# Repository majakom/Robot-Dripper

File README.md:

# Robot-Dripper

Project made for Computer System Architecture at Poznań University of Technology.

## General description of the project

The goal of this project was to create a robot that is a coffee machine.
Project was finally presented at Poznań Univeristy of Technology at the event RoboDay.

This repository includes code for both [arduino UNO prototype](motor_control) and [atmega 8 final version](ask) of the robot.<br />
[This directory](motiondetector) leads to code used for testing the motion detector.<br />
[Here](Eagle) You can find an Eagle board and schemtic for the PCB.

## Links to documentation

Entire documentation of the proccess available under the following link:<br />
https://docs.google.com/document/d/1cahnLlo-Lx6Y2TZ_qJPBwkHGlFsrj01b/edit?usp=sharing&ouid=103557156073634909180&rtpof=true&sd=true

Short film on YouTube which depicts the process of creating the coffee machine:<br />
https://www.youtube.com/watch?v=yFp_BpbxnpI

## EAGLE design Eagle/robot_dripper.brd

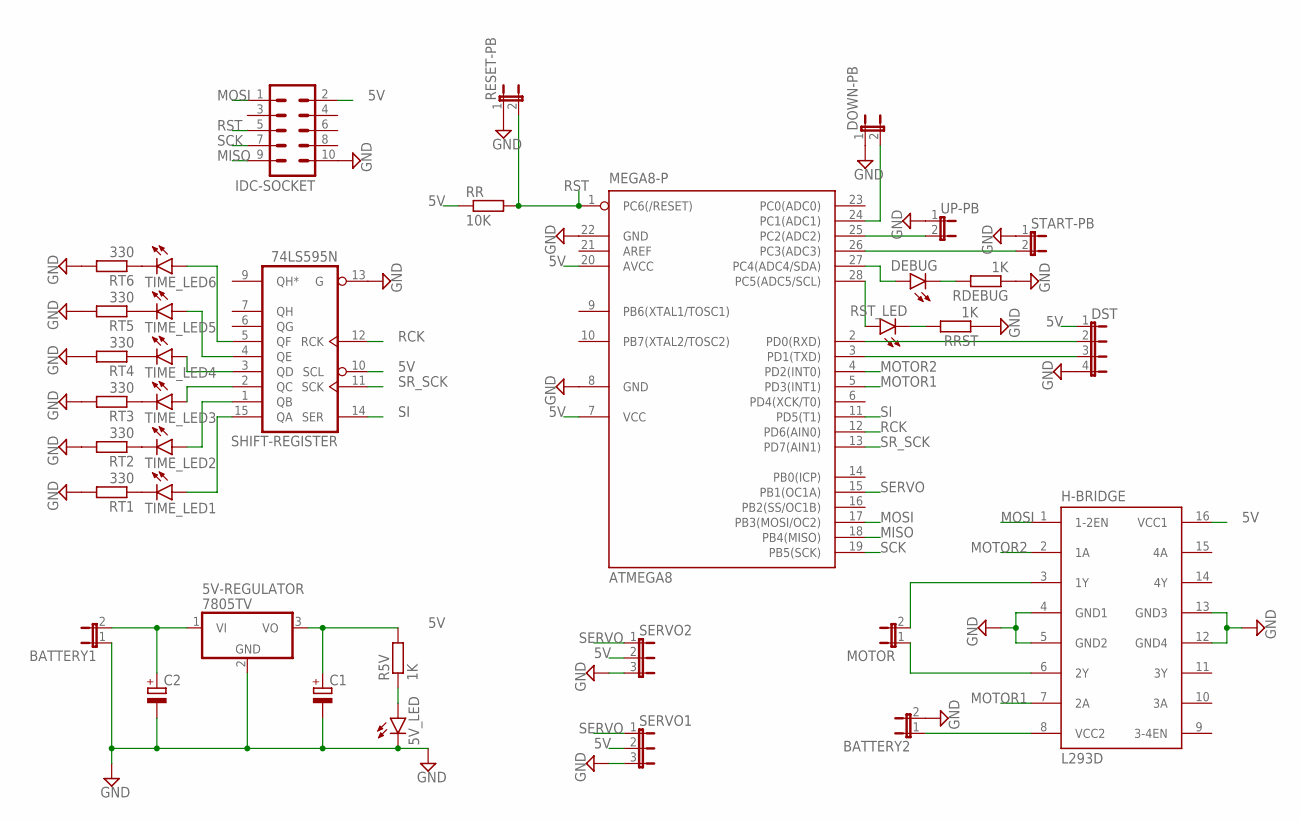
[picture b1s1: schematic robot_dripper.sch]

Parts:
5V-REGULATOR: 7805TV; TO220V
5V_LED: LED5MM
ATMEGA8: MEGA8-P; DIL28-3
BATTERY1, BATTERY2: JP1E; JP1
C1, C2: CPOL-EUE5-10.5; E5-10,5
DEBUG: LED5MM
DOWN-PB: JP1E; JP1
DST: JP4E; JP4
H-BRIDGE: L293D; DIL16
IDC-SOCKET: ML10
MOTOR: JP1E; JP1
R5V: 1K; 0207/10
RDEBUG: 1K; 0207/10
RESET-PB: JP1E; JP1
RR: 10K; 0207/10
RRST: 1K; 0207/10
RST_LED: LED5MM
RT1, RT2, RT3, RT4, RT5, RT6: 330; 0207/10
SERVO1, SERVO2: JP2E; JP2
SHIFT-REGISTER: 74LS595N; DIL16
START-PB: JP1E; JP1
TIME_LED1, TIME_LED2, TIME_LED3, TIME_LED4, TIME_LED5, TIME_LED6: LED5MM
UP-PB: JP1E; JP1

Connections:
5V: 5V-REGULATOR.3 (VO), ATMEGA8.7 (VCC), ATMEGA8.20 (AVCC), C1.+, DST.1, H-BRIDGE.16 (VCC1), IDC-SOCKET.2, R5V.2, RR.1, SERVO1.2, SERVO2.2, SHIFT-REGISTER.10 (SCL), SHIFT-REGISTER.16 (VCC)
GND: 5V-REGULATOR.2 (GND), 5V_LED.K (C), ATMEGA8.8 (GND), ATMEGA8.22 (GND), BATTERY1.1, BATTERY2.2, C1.-, C2.-, DOWN-PB.1, DST.4, H-BRIDGE.4 (GND1), H-BRIDGE.5 (GND2), H-BRIDGE.12 (GND4), H-BRIDGE.13 (GND3), IDC-SOCKET.10, RDEBUG.1, RESET-PB.1, RRST.1, RT1.2, RT2.2, RT3.2, RT4.2, RT5.2, RT6.2, SERVO1.3, SERVO2.3, SHIFT-REGISTER.8 (GND), SHIFT-REGISTER.13 (G), START-PB.1, UP-PB.1
MISO: ATMEGA8.18 (PB4(MISO)), IDC-SOCKET.9
MOSI: ATMEGA8.17 (PB3(MOSI/OC2)), H-BRIDGE.1 (1-2EN), IDC-SOCKET.1
MOTOR1: ATMEGA8.5 (PD3(INT1)), H-BRIDGE.7 (2A)
MOTOR2: ATMEGA8.4 (PD2(INT0)), H-BRIDGE.2 (1A)
unnamed: ATMEGA8.28 (PC5(ADC5/SCL)), RST_LED.A
unnamed: 5V_LED.A, R5V.1
unnamed: RRST.2, RST_LED.K (C)
unnamed: ATMEGA8.27 (PC4(ADC4/SDA)), DEBUG.A
unnamed: DEBUG.K (C), RDEBUG.2
unnamed: ATMEGA8.26 (PC3(ADC3)), START-PB.2
unnamed: ATMEGA8.25 (PC2(ADC2)), UP-PB.2
unnamed: ATMEGA8.24 (PC1(ADC1)), DOWN-PB.2
unnamed: ATMEGA8.2 (PD0(RXD)), DST.2
unnamed: ATMEGA8.3 (PD1(TXD)), DST.3
unnamed: H-BRIDGE.6 (2Y), MOTOR.1
unnamed: SHIFT-REGISTER.15 (QA), TIME_LED1.A
unnamed: SHIFT-REGISTER.1 (QB), TIME_LED2.A
unnamed: SHIFT-REGISTER.2 (QC), TIME_LED3.A
unnamed: H-BRIDGE.3 (1Y), MOTOR.2
unnamed: SHIFT-REGISTER.3 (QD), TIME_LED4.A
unnamed: SHIFT-REGISTER.4 (QE), TIME_LED5.A
unnamed: SHIFT-REGISTER.5 (QF), TIME_LED6.A
unnamed: RT1.1, TIME_LED1.K (C)
unnamed: RT2.1, TIME_LED2.K (C)
unnamed: RT3.1, TIME_LED3.K (C)
unnamed: RT4.1, TIME_LED4.K (C)
unnamed: RT5.1, TIME_LED5.K (C)
unnamed: RT6.1, TIME_LED6.K (C)
unnamed: BATTERY2.1, H-BRIDGE.8 (VCC2)
unnamed: 5V-REGULATOR.1 (VI), BATTERY1.2, C2.+
RCK: ATMEGA8.12 (PD6(AIN0)), SHIFT-REGISTER.12 (RCK)
RST: ATMEGA8.1 (PC6(/RESET)), IDC-SOCKET.5, RESET-PB.2, RR.2
SCK: ATMEGA8.19 (PB5(SCK)), IDC-SOCKET.7
SERVO: ATMEGA8.15 (PB1(OC1A)), SERVO1.1, SERVO2.1
SI: ATMEGA8.11 (PD5(T1)), SHIFT-REGISTER.14 (SER)
SR_SCK: ATMEGA8.13 (PD7(AIN1)), SHIFT-REGISTER.11 (SCK)

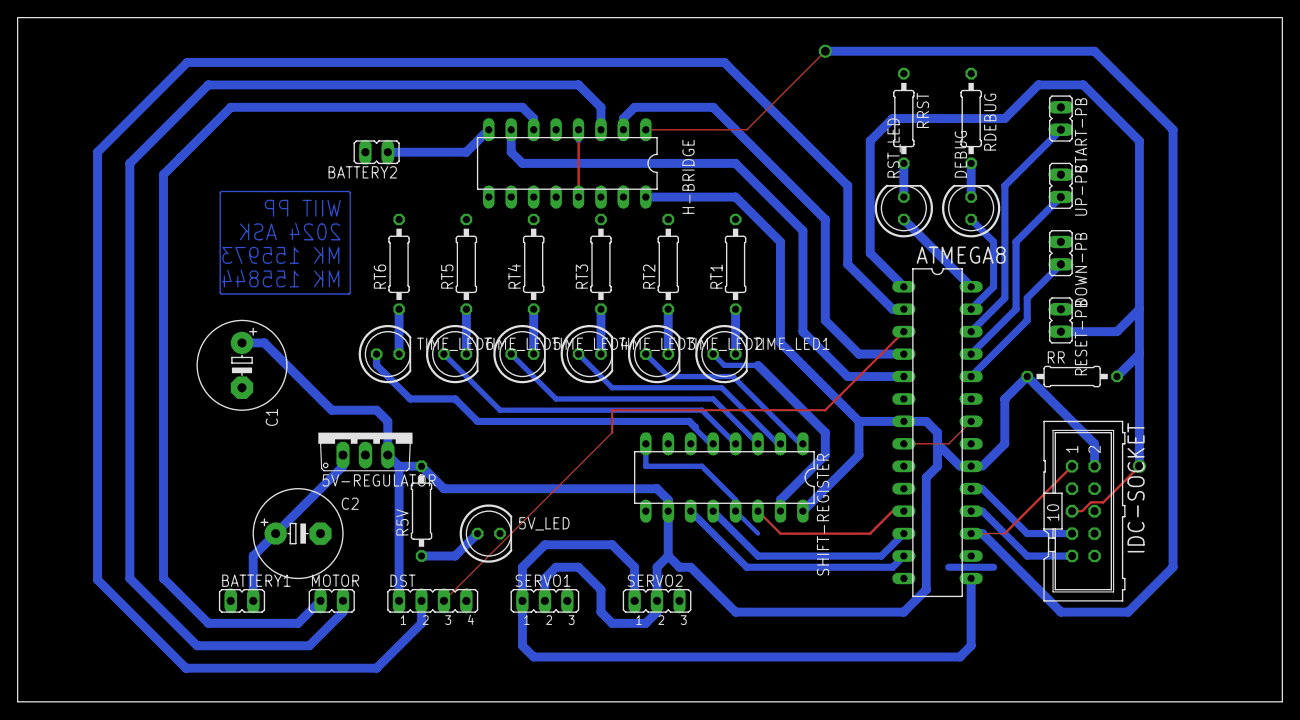
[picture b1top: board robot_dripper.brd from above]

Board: 2 copper layers, 143.2 x 77.5 mm, 36 parts (0 on the bottom side), 38 nets.

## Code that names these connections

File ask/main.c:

#include <avr/io.h>
#include <util/delay.h>
#include <avr/eeprom.h>
#include <stdio.h>
# define INDEX_DISTANCE 13
# define PROGRESS_STEPS 6

const int MIN_ANGLE = 41;
const int MAX_ANGLE = 3;

const int MAX_MOTOR = 140;
const int MIN_MOTOR = 105;

void init();
void initLEDs();
void initButtons();
void initServoControl();
void initDistanceMeasurement();
void initMotorControl();
void initShiftRegister();
void blinkResetLed();
void saveAngle();
void sendPulse();
unsigned long measurePulse();
unsigned long measureDistance();
void motorStop();
void motorForward(uint8_t dutyCycle);
void motorBackward(uint8_t dutyCycle);
void progressTime();
void writeShiftRegister();
void finishCoffee();
void startCoffee();
void servoUP();
void servoDOWN();
int distanceStop();
void stir1();
void stir2();

int stage = 0;
int distVector[INDEX_DISTANCE];
int indexVector = 0;
int stop = 0;
unsigned long distance = 0;
int progress = 0;


int main(void) {
	init();
	while(1) {
		saveAngle();
		distance = measureDistance();

		_delay_ms(1);
		switch (stage){
		case 0:
			if (bit_is_clear(PINC,PC3)){
				startCoffee();
				_delay_ms(30000);
				progressTime();
				_delay_ms(30000);
				progressTime();
			} else if (bit_is_clear(PINC,PC2)){
				servoUP();
			} else if (bit_is_clear(PINC,PC1)){
				servoDOWN();
			}
			break;
		case 1:
			stir1();
			_delay_ms(3000);
			break;
		case 2:
			stir2();
			_delay_ms(3000);
			break;
		case 3:
			motorStop();
			stage = 4;
			_delay_ms(2000);
			break;
		case 4:
			servoDOWN();
			stage = 5;
			break;
		case 5:
			PORTC |= (1<<PC4);
			_delay_ms(15000);
			progressTime();
			_delay_ms(30000);
			progressTime();
			_delay_ms(30000);
			progressTime();
			_delay_ms(30000);
			progressTime();
			PORTC &= ~(1<<PC4);
			stage = 6;
			break;
		case 6:
			servoUP();
			finishCoffee();
			progressTime();
			stage = 0;
			break;
		}
		_delay_ms(1);
	}
}

void init(void){
	initLEDs();
	initButtons();
	initServoControl();
	initDistanceMeasurement();
	initMotorControl();
	initShiftRegister();
	blinkResetLed();
}

void initLEDs(){
	DDRC |= (1<<PC5); // Set Reset Led Output
	DDRC |= (1<<PC4); // Set Debug Led Output
}

void initButtons(){
	DDRC &= ~(1<<PC3); // Set Start Button Input
	PORTC |= (1<<PC3); // Enale Start Button Pull-up
	DDRC &= ~(1<<PC2); // Set Servo-Up Button Input
	PORTC |= (1<<PC2); // Enable Servo-Up Button Pull-up
	DDRC &= ~(1<<PC1); // Set Servo-Down Button Input
	PORTC |= (1<<PC1); // Enable Servo-Down Button Pull-up
}

void initServoControl(){
	DDRB |= (1<<PB1); // Set Servo Pin
	// Set Timer
	TCCR1A |= (1<<COM1A1)|(1<<WGM11);
	TCCR1B |= (1<<WGM13)|(1<<WGM12)|(1<<CS11)|(1<<CS10);
	ICR1 = (F_CPU/64UL/60ul)-1;
	uint8_t byteRead = eeprom_read_byte((uint8_t*)23); // read the byte in location 23
	if (byteRead>=MAX_ANGLE && byteRead <= MIN_ANGLE){
		OCR1A = byteRead; // Set angle to last value (if in memory)
	} else {
		OCR1A = MAX_ANGLE; // Set default angle if nothing in memory
	}
}

void initDistanceMeasurement(){
	DDRD |= (1 << PD0); // Set trigger pin (PD0) as output
	DDRD &= ~(1 << PD1); // Set echo pin (PD1) as input
	for (int i = 0; i < INDEX_DISTANCE; i++){
		distVector[i] = 1000;
	}
}

void initMotorControl(){
	TCCR2 |= (1 << WGM20) | (1 << WGM21) | (1 << COM21) | (1 << CS22); // Set Fast PWM mode with non-inverted output
	DDRB |= (1 << PB3); // Set OC2 (PB3) as output
	DDRD |= (1<<PD2); // Set Direction 1 Control Output
	DDRD |= (1<<PD3); // Set Direction 2 Control Output
	OCR2 = 0;
	motorStop();
}

void initShiftRegister() {
	DDRD |= (1<<PD5); // Set SI/DS Output
	DDRD |= (1<<PD6); // Set RCK/ST_CP Output
	DDRD |= (1<<PD7); // Set SCK/SH_CP
	writeShiftRegister();
}

void blinkResetLed(){
	for (int i=0; i<10; i++){
		PORTC ^= (1<<PC5);
		_delay_ms(100);
	}
}

void saveAngle(){
	eeprom_write_byte ((uint8_t*) 23, OCR1A); //  write OCR1A (angle) to location 23 of the EEPROM
}

void sendPulse() {
    PORTD |= (1 << PD0); // Set trigger pin (PD0) HIGH
    _delay_us(10); // Wait for 10 microseconds
    PORTD &= ~(1 << PD0); // Set trigger pin LOW
}

unsigned long measurePulse() {
    unsigned long pulseDuration = 0;
    while (!(PIND & (1 << PD1))); // Wait for the echo pin to go HIGH
    while (PIND & (1 << PD1)) pulseDuration++; // Measure pulse duration
    return pulseDuration;
}

unsigned long measureDistance(){
	sendPulse(); // Send pulse to trigger the sensor
	unsigned long duration = measurePulse(); // Measure the pulse duration
	// Calculate distance using duration and the speed of sound
	unsigned long new_distance = (duration * 343) / (2*1000); // Convert to centimeters

	if (indexVector == INDEX_DISTANCE){
		indexVector = 0;
	}
	distVector[indexVector++] = distance;
	return new_distance;
}

void motorStop(){
	OCR2 = 0;
	PORTD &= ~(1<<PD2);
	PORTD &= ~(1<<PD3);
}
void motorForward(uint8_t dutyCycle){
	PORTD &= ~(1<<PD2);
	PORTD |= (1<<PD3);
	OCR2 = dutyCycle;

}
void motorBackward(uint8_t dutyCycle){
	PORTD &= ~(1<<PD3);
	PORTD |= (1<<PD2);
	OCR2 = dutyCycle;
}

void startCoffee(){
	PORTC |= (1<<PC4);
	servoUP();
	stage = 1;
}

void servoUP(){
	for (int i = OCR1A; i >= MAX_ANGLE; i--){
		OCR1A = i;
		_delay_ms(100);
		saveAngle();
	}
	saveAngle();
}

void servoDOWN(){
	for (int i = 0; i < INDEX_DISTANCE; i++){
		distVector[i] = 1000;
	}
	_delay_ms(10);
	for (int i = OCR1A; i <= MIN_ANGLE; i++){
		if (!distanceStop()){
			OCR1A = i;
			_delay_ms(90);
			saveAngle();
		}
		else {
			saveAngle();
			break;
		}
	}
}

int distanceStop(){
	distance = measureDistance();
	int stop = 1;
	for(int j = 0; j < INDEX_DISTANCE; j++) {
		if(distVector[j] > 6) {
			stop = 0;
		}
	}
	return stop;
}

void stir1(){
	PORTC &= ~(1<<PC4);
	motorStop();
	_delay_ms(50);
	motorForward(MAX_MOTOR);
	_delay_ms(2000);
	for (int i = MAX_MOTOR; i >= MIN_MOTOR; i--){
		motorForward(i);
		_delay_ms(10);
	}
	motorStop();
	_delay_ms(1000);
	stage = 2;
}

void stir2(){
	motorStop();
	_delay_ms(50);
	motorBackward(MAX_MOTOR);
	_delay_ms(1000);
	for (int i = MAX_MOTOR; i >= MIN_MOTOR; i--){
		motorBackward(i);
		_delay_ms(10);
	}
	stage = 3;
}

void progressTime() {
	progress++;
	if (progress == PROGRESS_STEPS+1) {
		progress = 0;
	}
	writeShiftRegister();
}

void writeShiftRegister(){
	PORTD &= ~(1<<PD6);
	if (progress){
		PORTD &= ~(1<<PD7);
		PORTD |= (1<<PD5);
		PORTD |= (1<<PD7);
	} else {
		PORTD &= ~(1<<PD5);
		for (int i = 0; i<8; i++){
			PORTD &= ~(1<<PD7);
			PORTD |= (1<<PD7);
		}
	}
	PORTD |= (1<<PD6);
}

void finishCoffee(){
	for (int j = 0; j < 10; j++){
		for (int i = 0; i < PROGRESS_STEPS; i++){
			PORTD &= ~(1<<PD6);
			PORTD &= ~(1<<PD7);
			PORTD |= (1<<PD5);
			PORTD |= (1<<PD7);
			PORTD |= (1<<PD6);
			_delay_ms(35);
		}
		for (int i = 0; i < PROGRESS_STEPS; i++){
			PORTD &= ~(1<<PD6);
			PORTD &= ~(1<<PD7);
			PORTD &= ~(1<<PD5);
			PORTD |= (1<<PD7);
			PORTD |= (1<<PD6);
			_delay_ms(35);
		}
	}

}

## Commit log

2024-03-08 Added simple code for detecting motion
2024-03-22 Added motor controler
2024-03-22 Added H-bridge
2024-03-22 Added servo
2024-04-12 Changed code for servo control
2024-04-12 Added debug and break
2024-04-13 Added button for reset
2024-04-13 final_prototype
2024-04-14 Changed timeWait
2024-04-17 main for atmega8a
2024-04-18 Added shift
2024-04-18 Adjusted params
2024-05-03 final code with good params
2024-05-04 Adjusted params again
2024-05-05 Fixed misspelling
2024-08-02 Changed readme
2024-08-02 Added Eagle board and schematic
